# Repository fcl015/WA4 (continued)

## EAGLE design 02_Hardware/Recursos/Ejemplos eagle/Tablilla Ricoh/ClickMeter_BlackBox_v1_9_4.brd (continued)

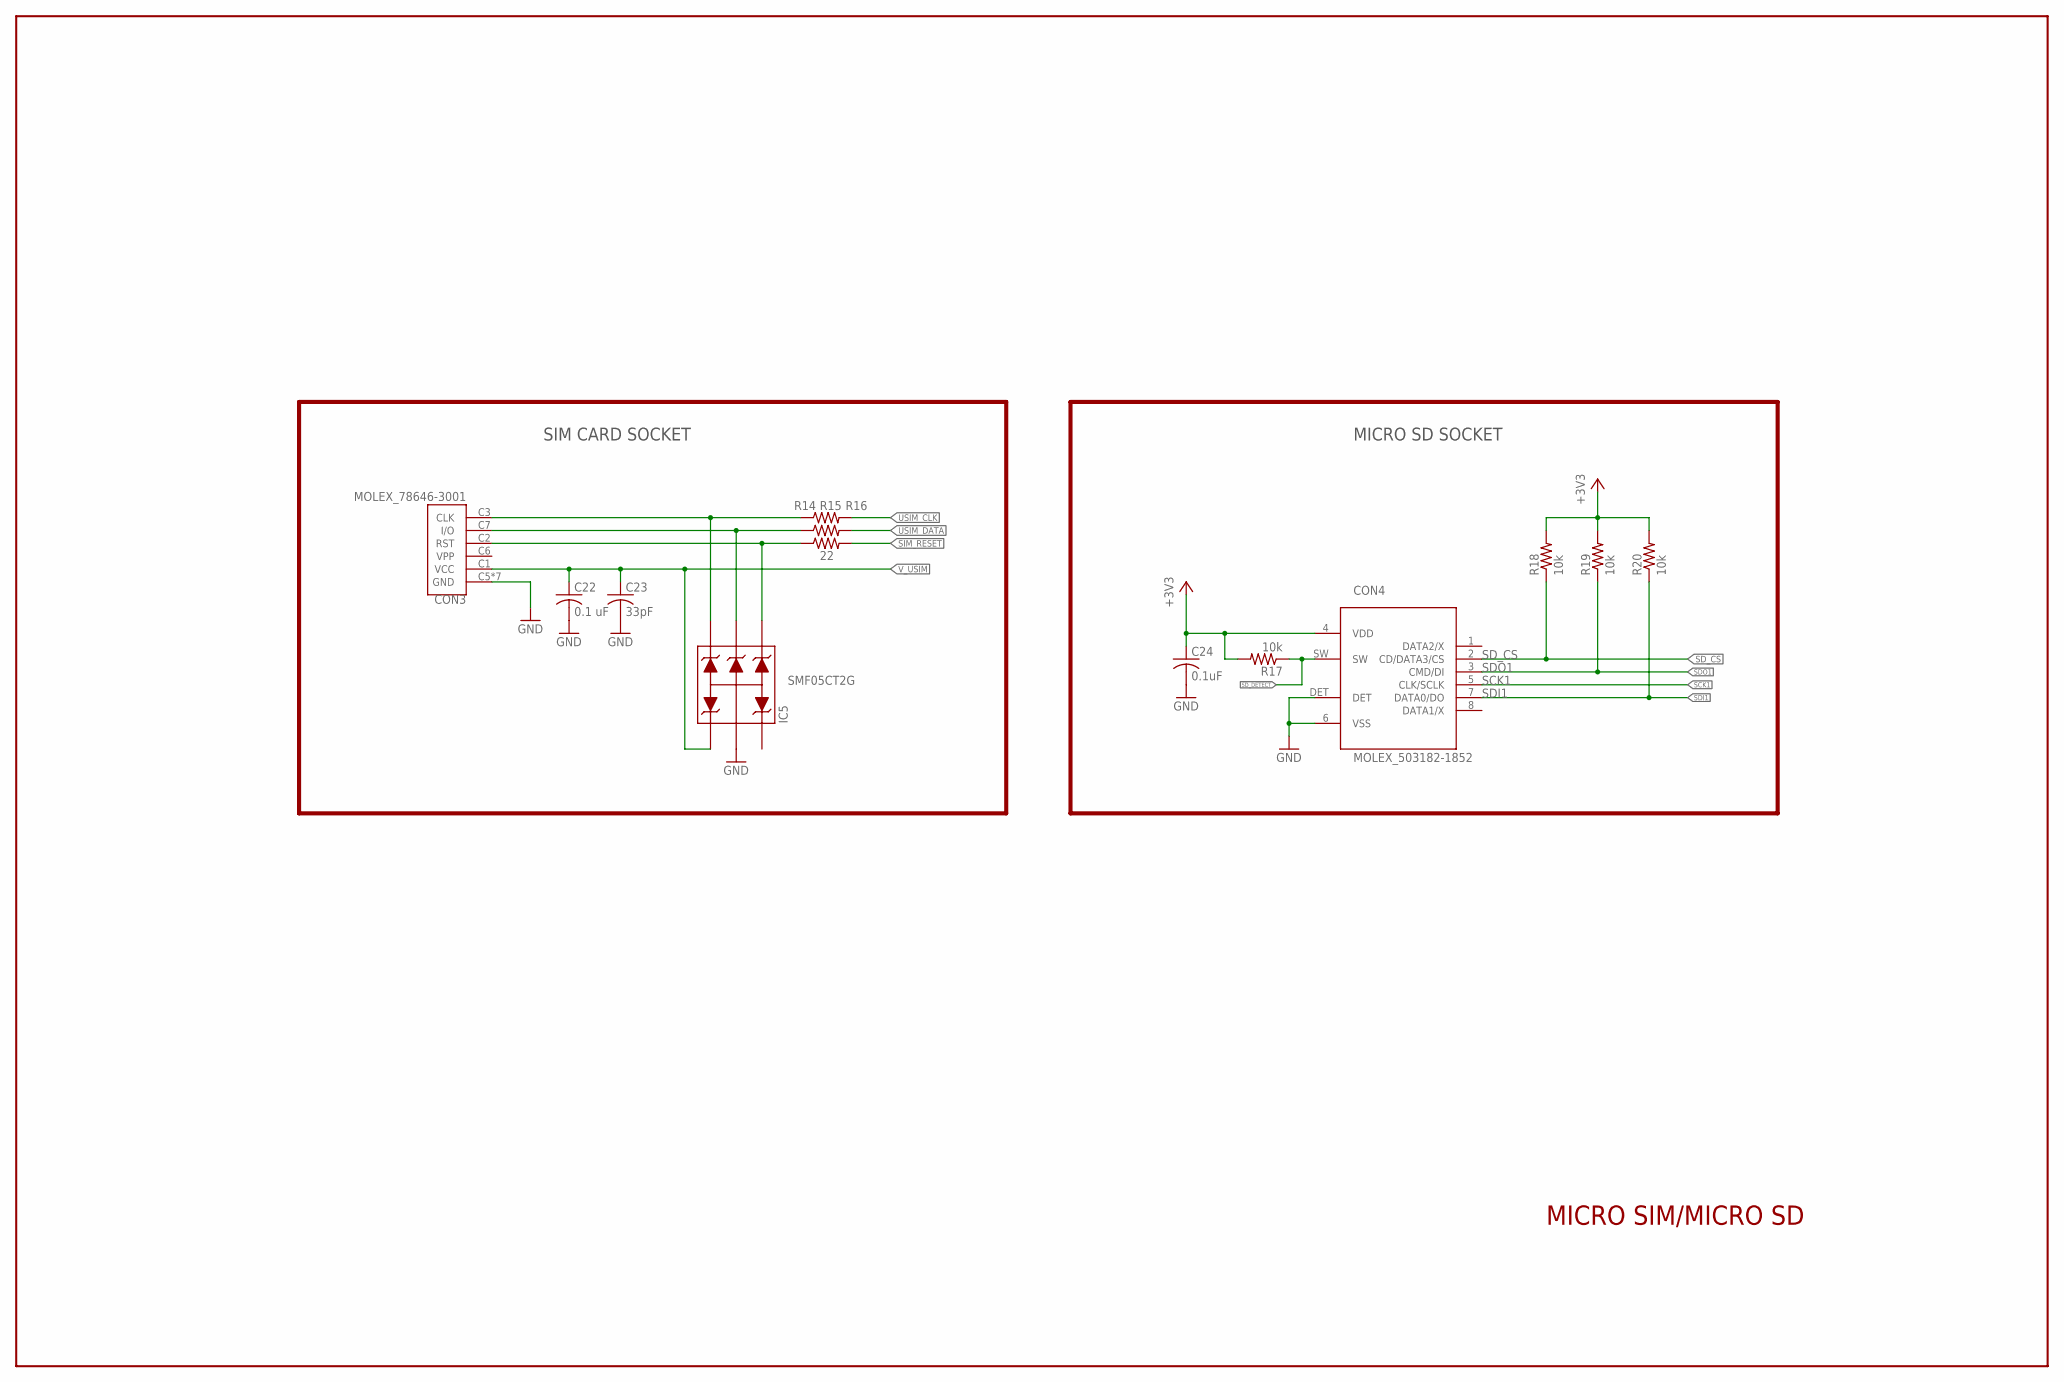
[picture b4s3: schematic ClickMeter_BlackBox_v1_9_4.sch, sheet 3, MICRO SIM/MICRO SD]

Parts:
C22: 0.1 uF; C0603
C23: 33pF; C0603
C24: 0.1uF; C0603
CON3: MOLEX_78646-3001
CON4: MOLEX_503182-1852
IC5: SMF05CT2G; SC-88/SC70-6/SOT-363
R14, R15, R16: 22; R0603
R17, R18, R19, R20: 10k; R0603

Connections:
+3V3: C24.1, CON4.4 (VDD), R17.2, R18.2, R19.2, R20.2; also elsewhere on the board
GND: C22.2, C23.2, C24.2, CON3.C5 (GND), CON3.GND1 (GND), CON3.GND2 (GND), CON3.GND3 (GND), CON3.GND4 (GND), CON3.GND5 (GND), CON3.GND6 (GND), CON4.6 (VSS), CON4.DET, IC5.2 (AN); also elsewhere on the board
unnamed: CON3.C3 (CLK), IC5.6 (C5), R14.1
unnamed: CON3.C7 (I/O), IC5.5 (C4), R15.1
unnamed: CON3.C2 (RST), IC5.4 (C3), R16.1
SCK1: CON4.5 (CLK/SCLK); also elsewhere on the board
SDI1: CON4.7 (DATA0/DO), R20.1; also elsewhere on the board
SDO1: CON4.3 (CMD/DI), R19.1; also elsewhere on the board
SD_CS: CON4.2 (CD/DATA3/CS), R18.1; also elsewhere on the board
SD_DETECT: CON4.SW, R17.1; also elsewhere on the board
SIM_RESET: R16.2; also elsewhere on the board
USIM_CLK: R14.2; also elsewhere on the board
USIM_DATA: R15.2; also elsewhere on the board
V_USIM: C22.1, C23.1, CON3.C1 (VCC), IC5.1 (C1); also elsewhere on the board

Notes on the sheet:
SIM CARD SOCKET
MICRO SD SOCKET
MICRO SIM/MICRO SD

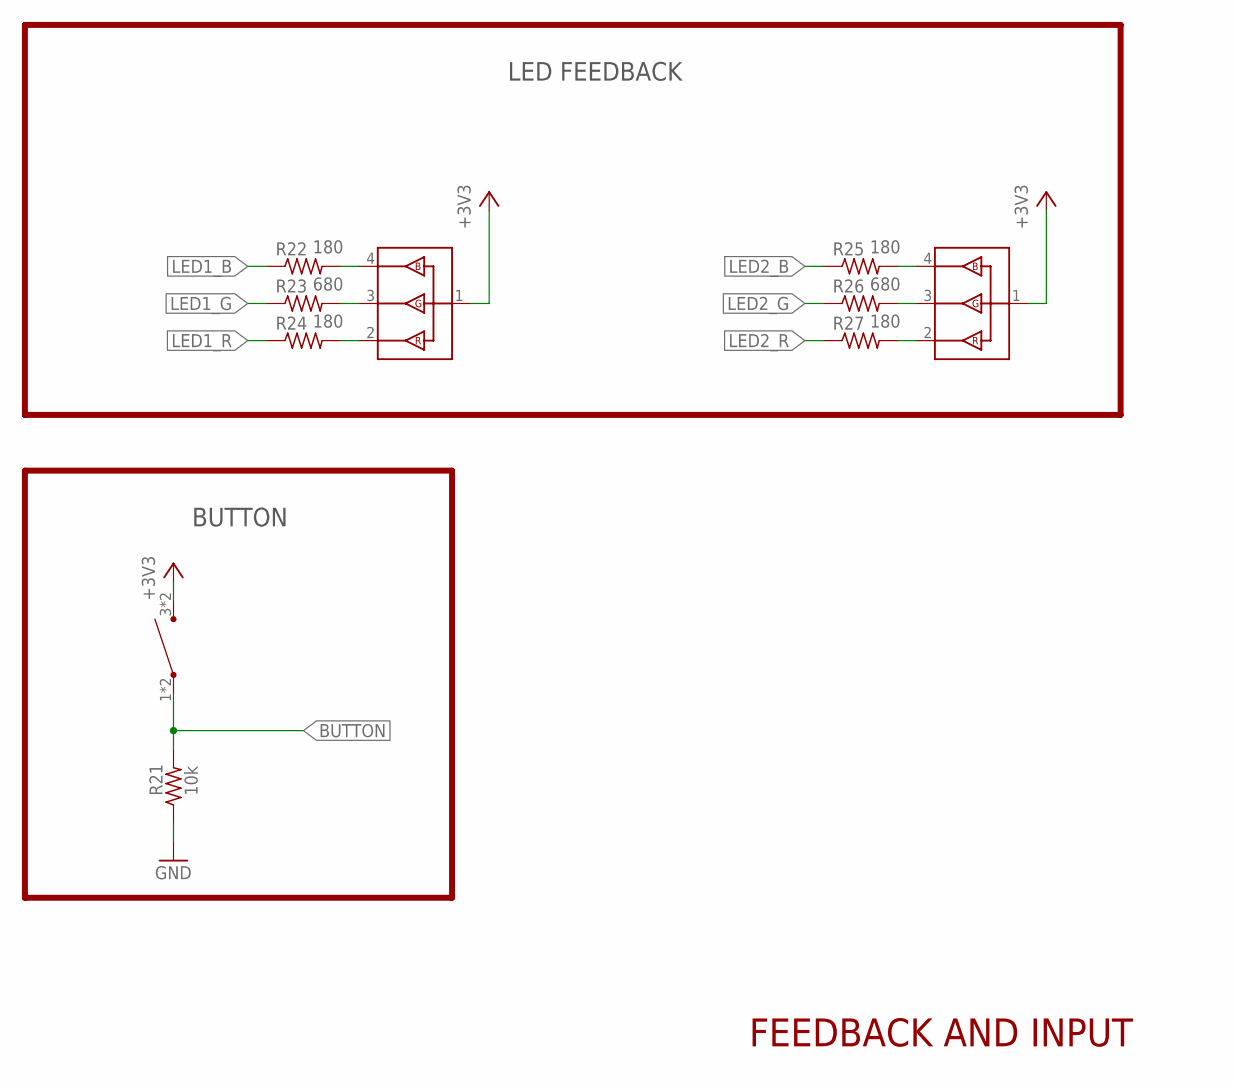
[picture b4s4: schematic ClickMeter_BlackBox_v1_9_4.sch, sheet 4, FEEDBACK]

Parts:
BT1: PTS525_SM15; PTS525SM15SMTR2
LED1, LED2: APTF1616SEEZGQBDC
R21: 10k; R0603
R22, R24, R25, R27: 180; R0603
R23, R26: 680; R0603

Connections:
+3V3: BT1.3, BT1.4, LED1.1, LED2.1; also elsewhere on the board
BUTTON: BT1.1, BT1.2, R21.2; also elsewhere on the board
GND: R21.1; also elsewhere on the board
LED1_B: R22.1; also elsewhere on the board
LED1_G: R23.1; also elsewhere on the board
LED1_R: R24.1; also elsewhere on the board
LED2_B: R25.1; also elsewhere on the board
LED2_G: R26.1; also elsewhere on the board
LED2_R: R27.1; also elsewhere on the board
unnamed: LED1.3, R23.2
unnamed: LED1.2, R24.2
unnamed: LED1.4, R22.2
unnamed: LED2.3, R26.2
unnamed: LED2.2, R27.2
unnamed: LED2.4, R25.2

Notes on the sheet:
FEEDBACK AND INPUT
LED FEEDBACK
BUTTON

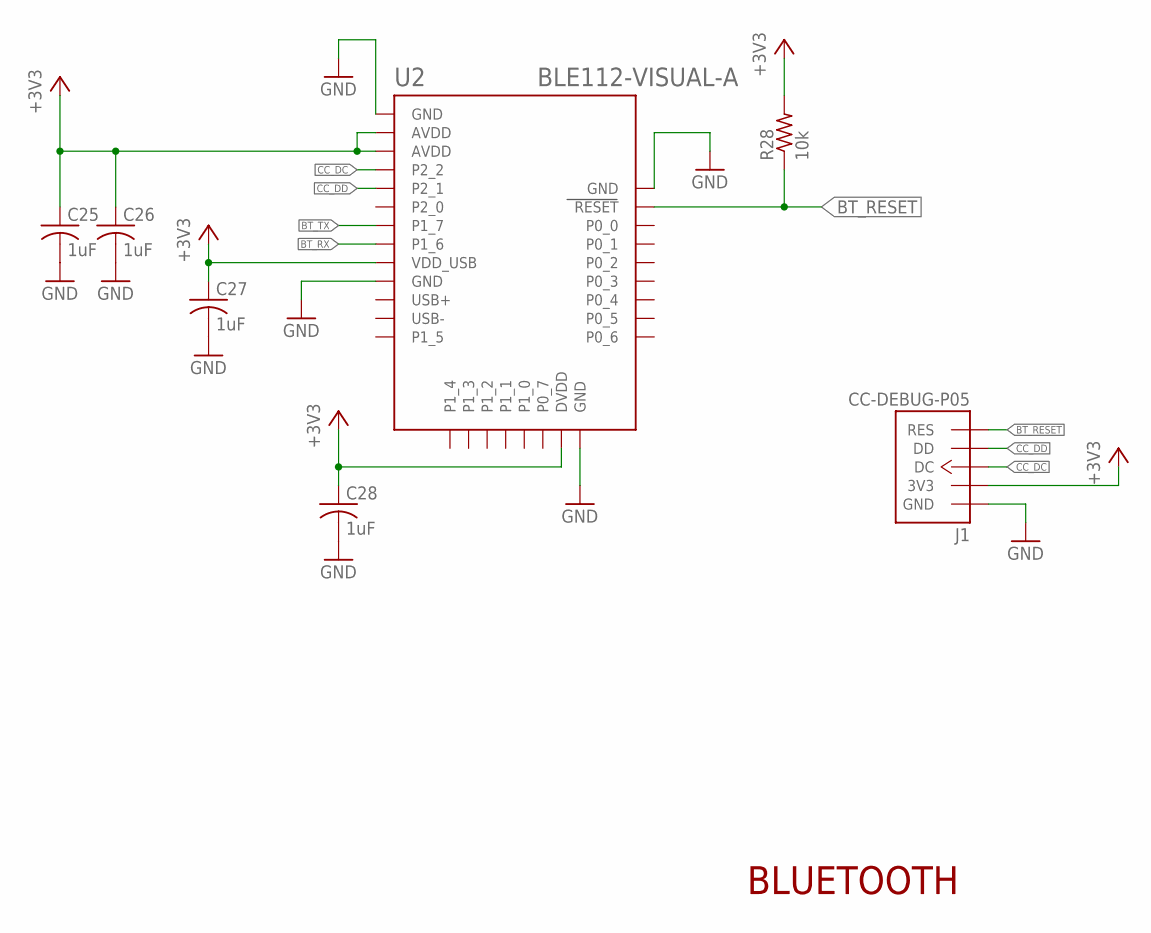
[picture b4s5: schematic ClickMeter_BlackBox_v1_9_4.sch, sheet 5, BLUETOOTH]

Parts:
C25, C26, C27, C28: 1uF; C0603
J1: CC-DEBUG-P05; CC-P05
R28: 10k; R0603
U2: BLE112-VISUAL-A; BLE112-A

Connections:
+3V3: C25.1, C26.1, C27.1, C28.1, J1.2 (3V3), R28.2, U2.AVDD, U2.AVDD@2 (AVDD), U2.DVDD, U2.VDD_USB; also elsewhere on the board
BT_RESET: J1.7 (RES), R28.1, U2.RESET; also elsewhere on the board
BT_RX: U2.P1_6; also elsewhere on the board
BT_TX: U2.P1_7; also elsewhere on the board
CC_DC: J1.3 (DC), U2.P2_2
CC_DD: J1.4 (DD), U2.P2_1
GND: C25.2, C26.2, C27.2, C28.2, J1.1 (GND), U2.GND, U2.GND@2 (GND), U2.GND@3 (GND), U2.GND@4 (GND); also elsewhere on the board

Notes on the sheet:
BLUETOOTH

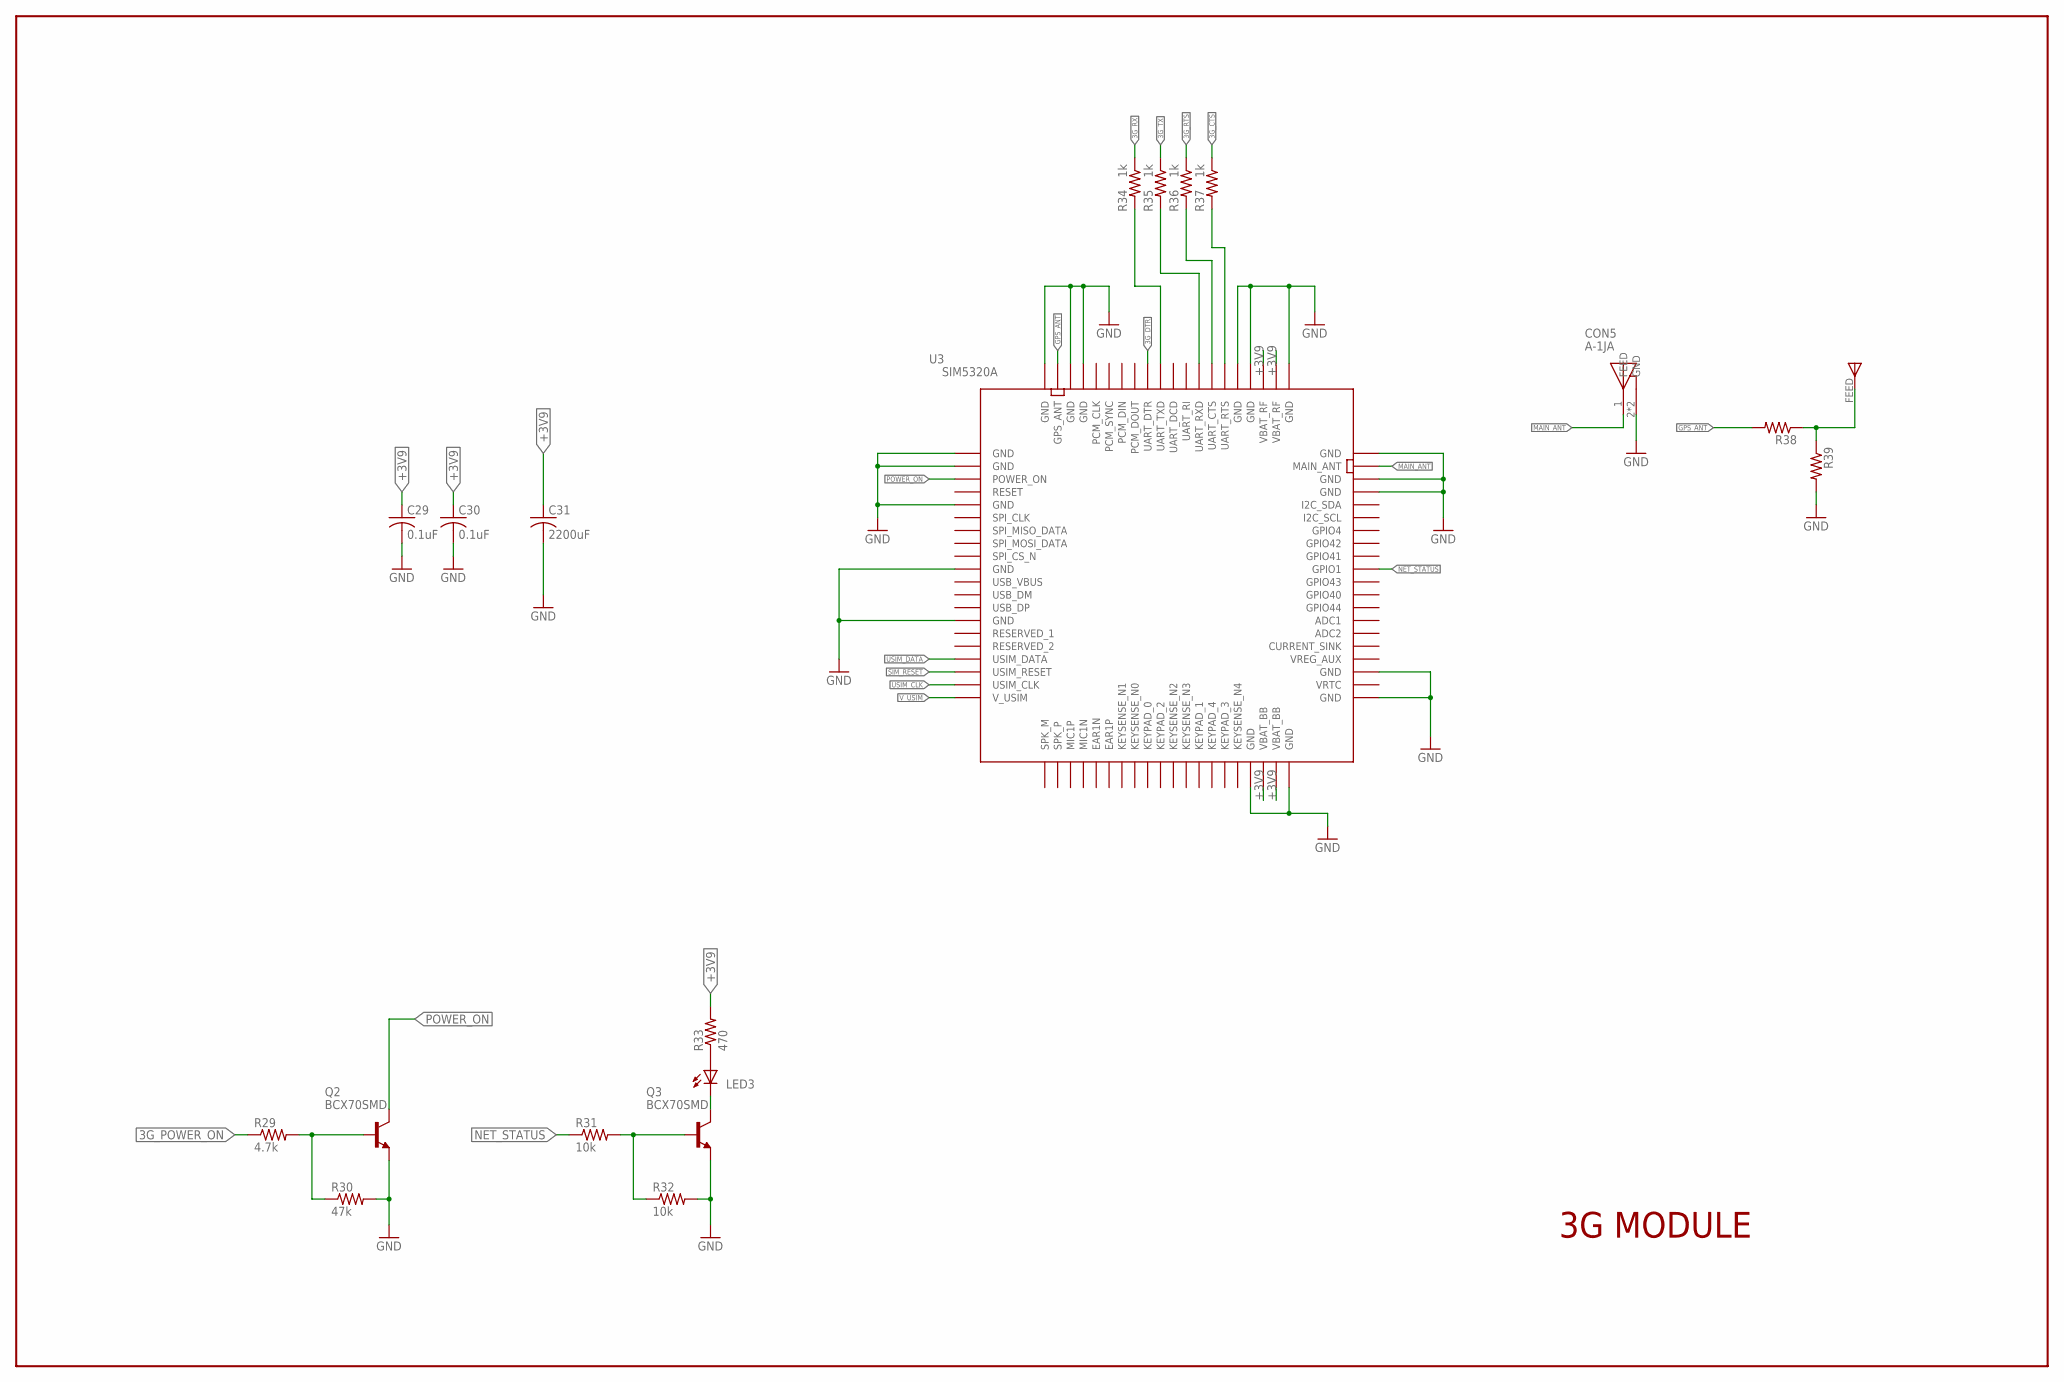
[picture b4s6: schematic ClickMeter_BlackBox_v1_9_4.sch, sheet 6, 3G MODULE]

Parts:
ANT1: 1575AT43A0040E
C29, C30: 0.1uF; C0603
C31: 2200uF; 592D-2200
CON5: A-1JA
LED3: LED_ESML0603; LED_SML0603
Q2, Q3: BCX70SMD; SOT23
R29: 4.7k; R0603
R30: 47k; R0603
R31, R32: 10k; R0603
R33: 470; R0603
R34, R35, R36, R37: 1k; R0402
R38, R39: R-US_R0402; R0402
U3: SIM5320A

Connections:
3G_CTS: R37.1; also elsewhere on the board
3G_DTR: U3.P$72 (UART_DTR); also elsewhere on the board
3G_POWER_ON: R29.1; also elsewhere on the board
3G_RTS: R36.1; also elsewhere on the board
3G_RX: R34.1; also elsewhere on the board
3G_TX: R35.1; also elsewhere on the board
+3V9: C29.1, C30.1, C31.1, R33.2, U3.P$38 (VBAT_BB), U3.P$39 (VBAT_BB), U3.P$62 (VBAT_RF), U3.P$63 (VBAT_RF); also elsewhere on the board
GND: C29.2, C30.2, C31.2, CON5.2 (GND), CON5.3 (GND), Q2.2 (E), Q3.2 (E), R30.2, R32.2, R39.2, U3.P$1 (GND), U3.P$2 (GND), U3.P$5 (GND), U3.P$10 (GND), U3.P$14 (GND), U3.P$37 (GND), U3.P$40 (GND), U3.P$41 (GND), U3.P$43 (GND), U3.P$57 (GND), U3.P$58 (GND), U3.P$60 (GND), U3.P$61 (GND), U3.P$64 (GND), U3.P$65 (GND), U3.P$77 (GND), U3.P$78 (GND), U3.P$80 (GND); also elsewhere on the board
GPS_ANT: R38.2, U3.P$79 (GPS_ANT)
MAIN_ANT: CON5.1 (FEED), U3.P$59 (MAIN_ANT)
unnamed: R34.2, U3.P$71 (UART_TXD)
unnamed: Q2.1 (B), R29.2, R30.1
unnamed: Q3.1 (B), R31.2, R32.1
unnamed: LED3.A, R33.1
unnamed: LED3.C, Q3.3 (C)
unnamed: ANT1.FEED, R38.1, R39.1
unnamed: R35.2, U3.P$68 (UART_RXD)
unnamed: R36.2, U3.P$67 (UART_CTS)
unnamed: R37.2, U3.P$66 (UART_RTS)
NET_STATUS: R31.1, U3.P$51 (GPIO1); also elsewhere on the board
POWER_ON: Q2.3 (C), U3.P$3 (POWER_ON)
SIM_RESET: U3.P$18 (USIM_RESET); also elsewhere on the board
USIM_CLK: U3.P$19 (USIM_CLK); also elsewhere on the board
USIM_DATA: U3.P$17 (USIM_DATA); also elsewhere on the board
V_USIM: U3.P$20 (V_USIM); also elsewhere on the board

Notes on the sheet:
3G MODULE

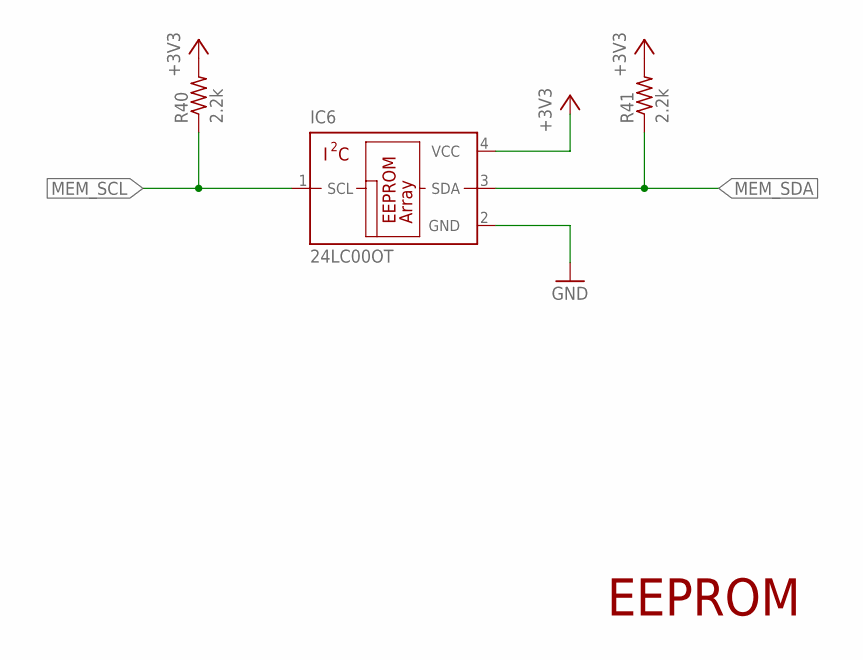
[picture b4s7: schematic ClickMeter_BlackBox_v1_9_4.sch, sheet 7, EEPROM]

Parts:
IC6: 24LC00OT; SOT23-5L
R40, R41: 2.2k; R0603

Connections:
+3V3: IC6.4 (VCC), R40.2, R41.2; also elsewhere on the board
GND: IC6.2 (GND); also elsewhere on the board
MEM_SCL: IC6.1 (SCL), R40.1; also elsewhere on the board
MEM_SDA: IC6.3 (SDA), R41.1; also elsewhere on the board

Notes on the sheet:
EEPROM

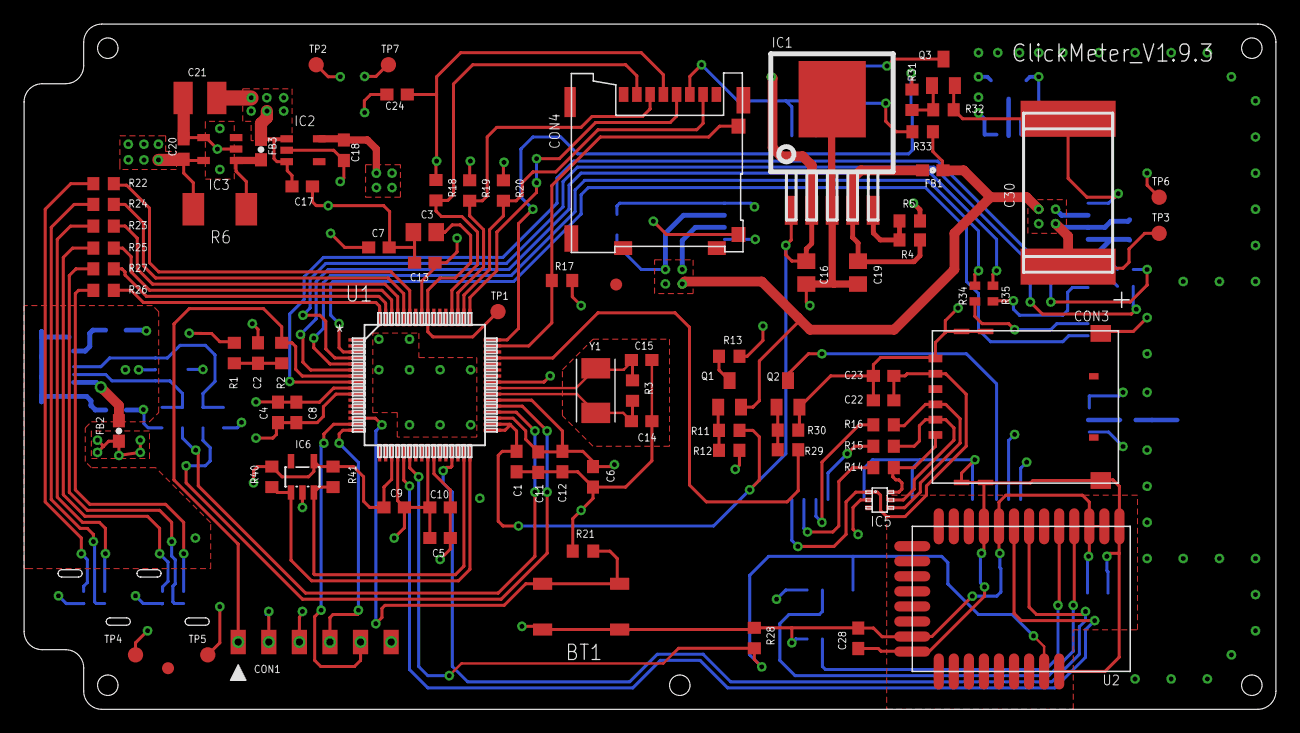
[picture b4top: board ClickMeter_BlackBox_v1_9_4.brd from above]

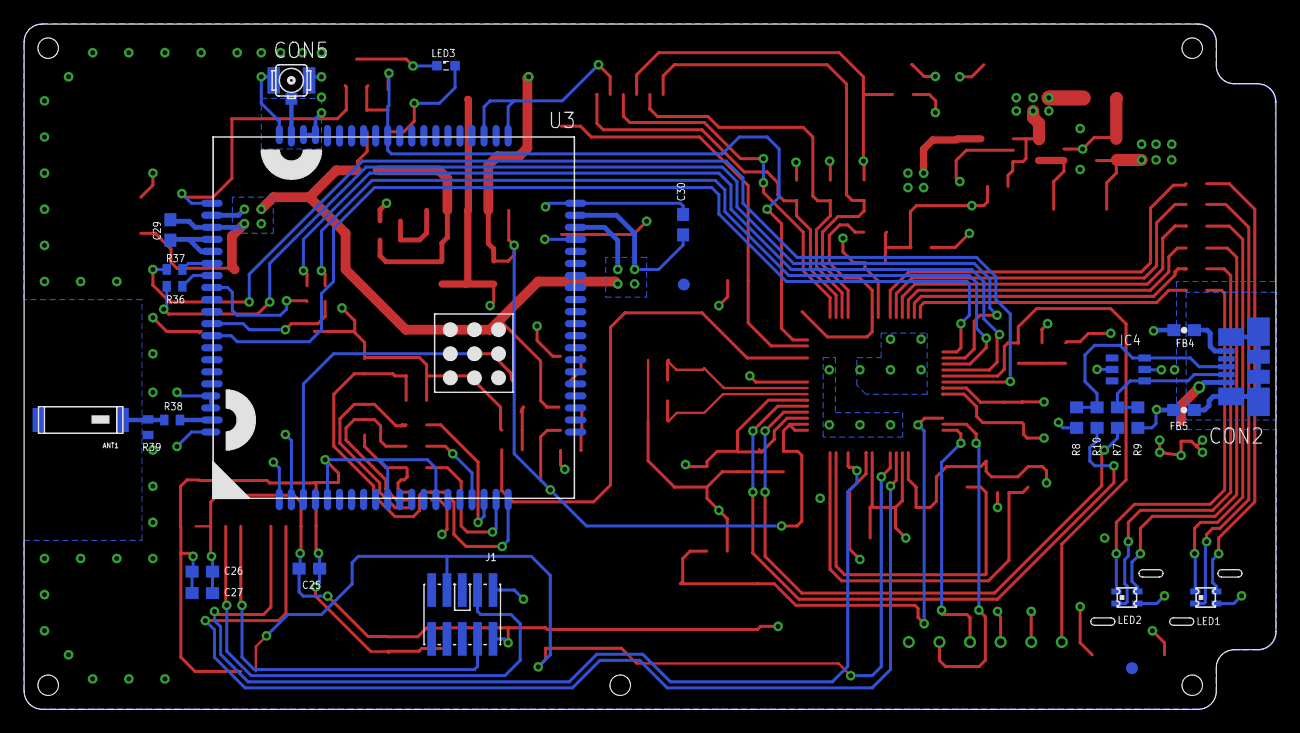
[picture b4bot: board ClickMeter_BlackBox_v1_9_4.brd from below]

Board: 4 copper layers, 104.0 x 56.9 mm, 112 parts (26 on the bottom side), 75 nets.

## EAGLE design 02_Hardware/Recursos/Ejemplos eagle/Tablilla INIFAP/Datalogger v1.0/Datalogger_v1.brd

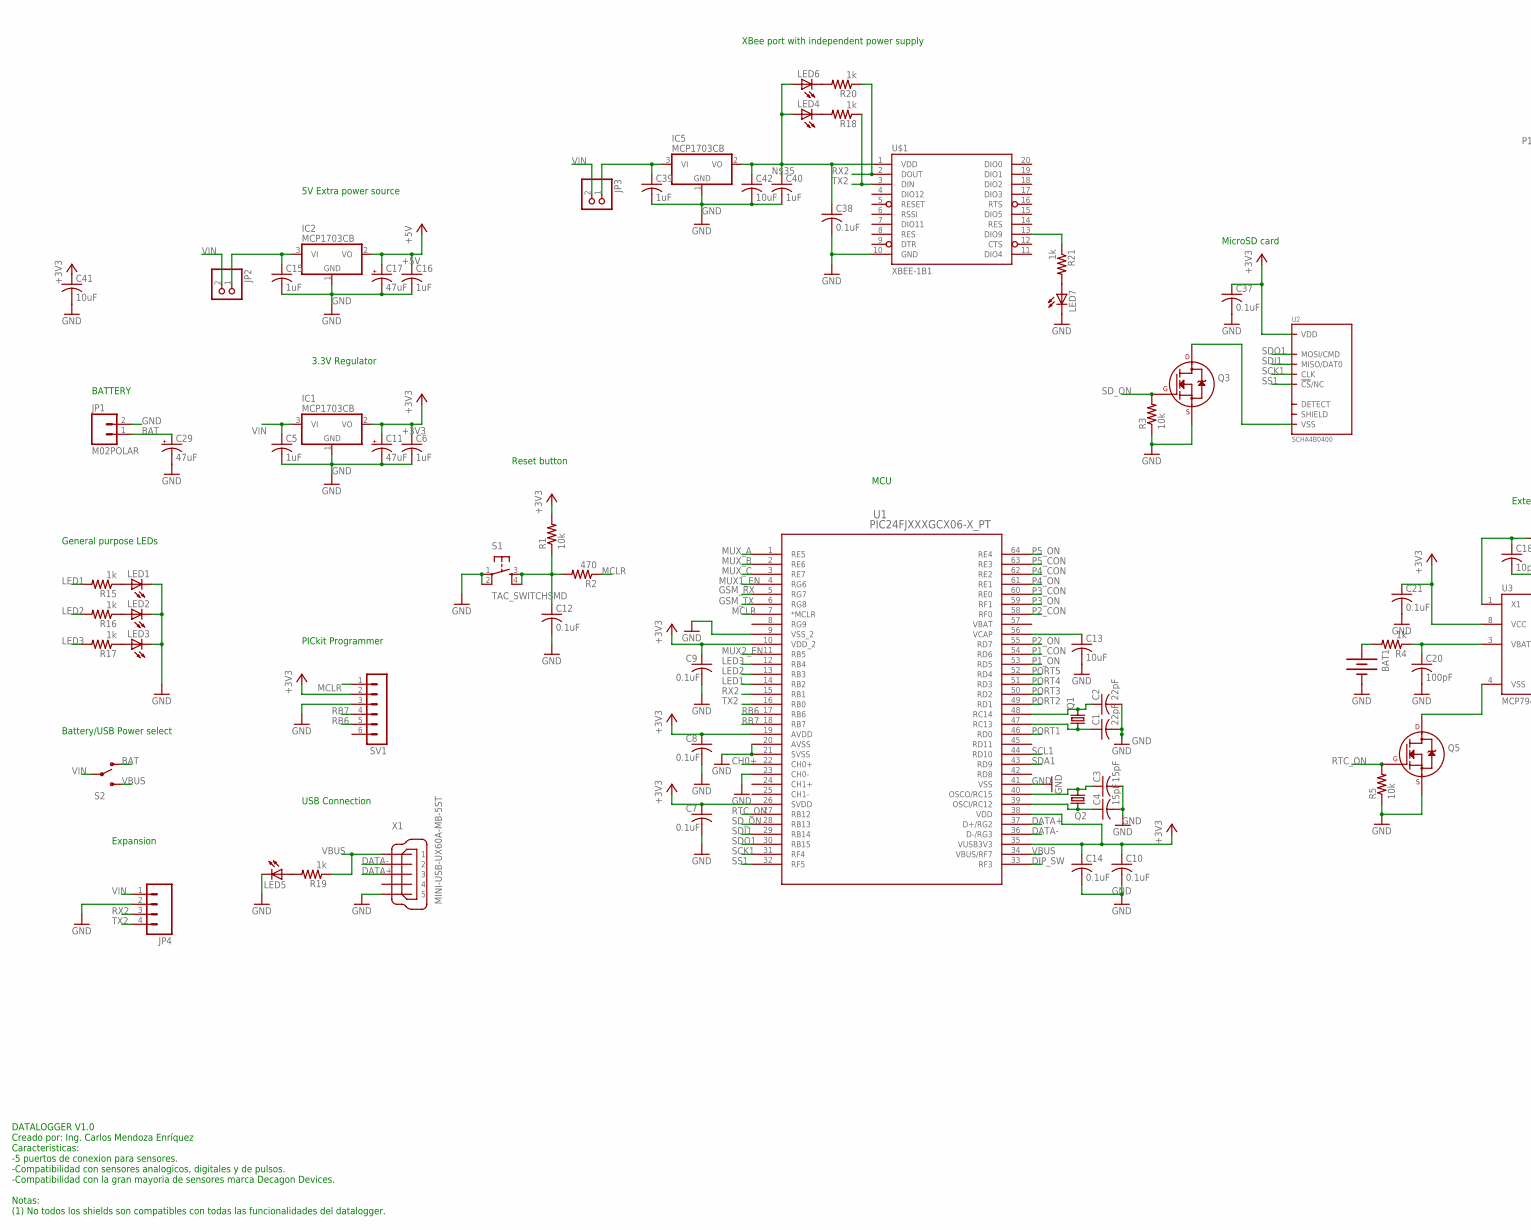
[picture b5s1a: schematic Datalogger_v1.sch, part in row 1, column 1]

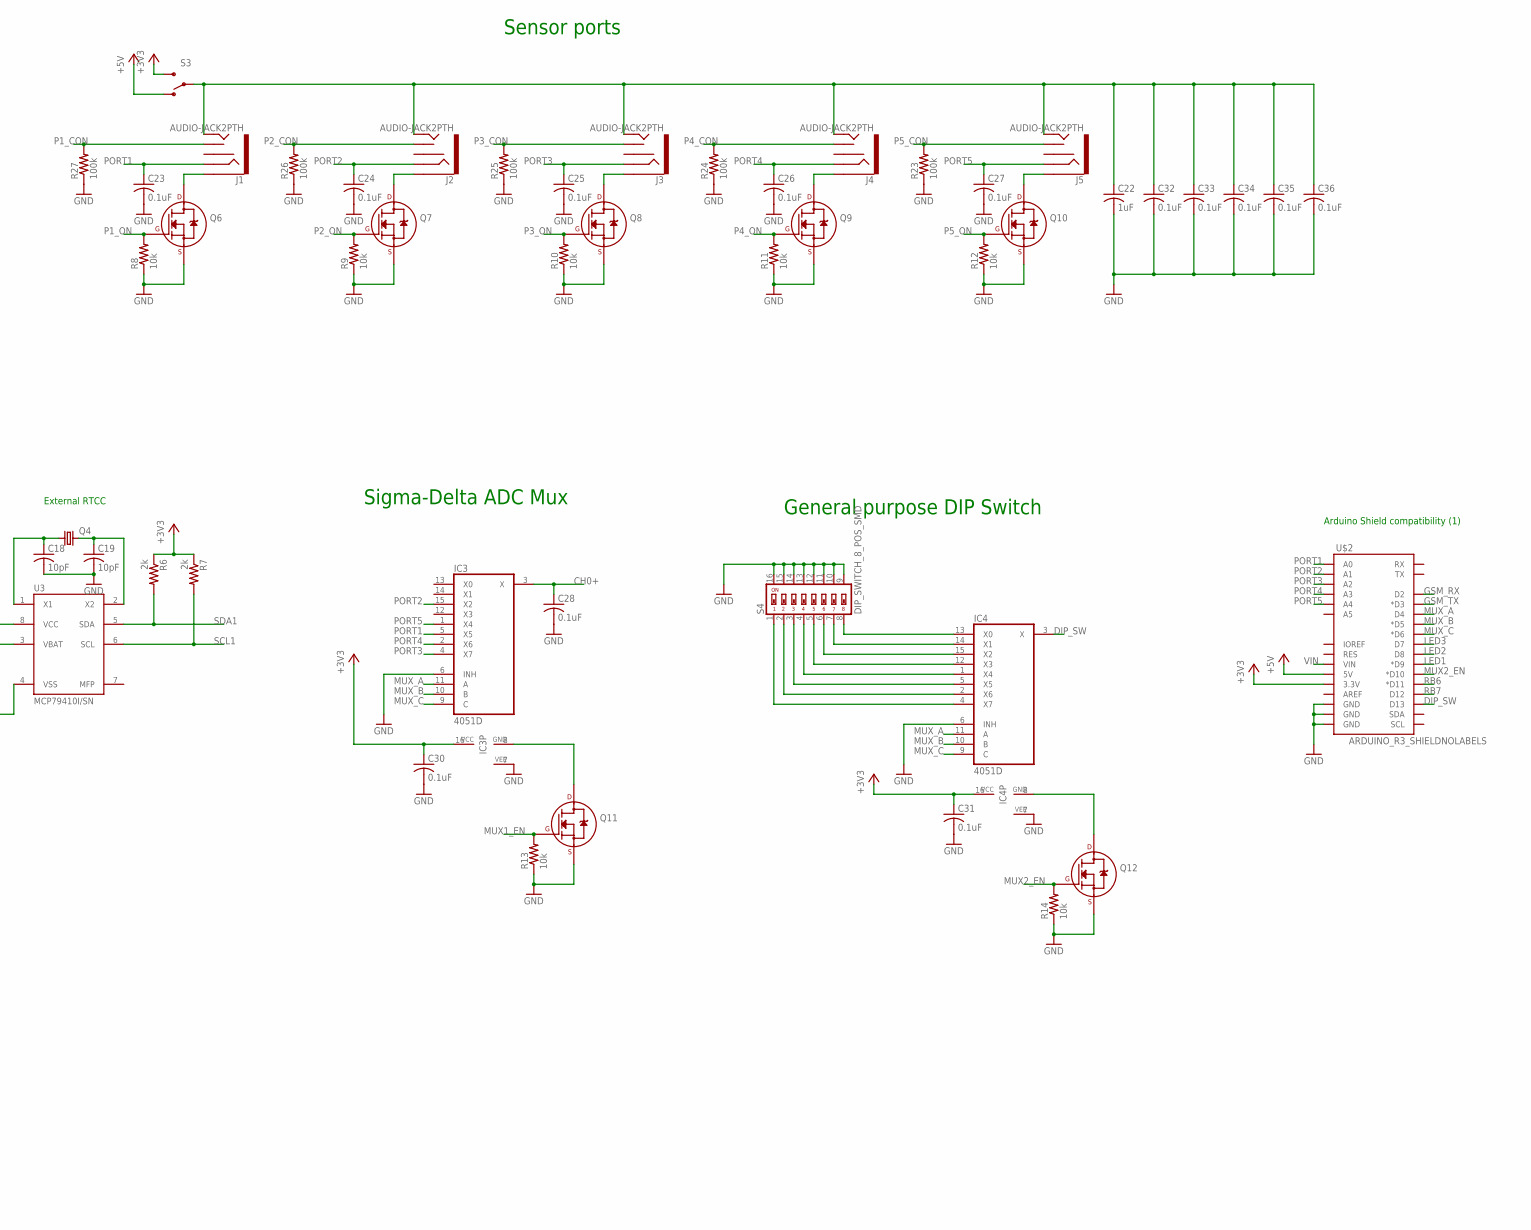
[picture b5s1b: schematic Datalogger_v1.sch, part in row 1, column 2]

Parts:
BAT1: BATTERY20PTH; BATTCOM_20MM_PTH
C1, C2: 22pF; C0603K
C3, C4: 15pF; C0603K
C5, C6, C15, C16, C22, C39, C40: 1uF; C0805K
C7, C8, C9, C10, C12, C14, C21, C23, C24, C25, C26, C27, C28, C30, C31, C32, C33, C34, C35, C36, C37, C38: 0.1uF; C0805K
C11, C17, C29: 47uF; 153CLV-0605
C13, C41, C42: 10uF; C0805K
C18, C19: 10pF; C0603K
C20: 100pF; C0805K
IC1, IC2, IC5: MCP1703CB; SOT23
IC3, IC4: 4051D; SO16
J1, J2, J3, J4, J5: AUDIO-JACK2PTH; AUDIO-JACK
JP1: M02POLAR; MOLEX-1X2
JP2, JP3: PINHD-1X2; 1X02
JP4: M04POLAR; MOLEX-1X4
LED1, LED2, LED3, LED4, LED5, LED6, LED7: LEDCHIPLED_0603; CHIPLED_0603
Q1, Q4: CRYSTALMM20SS; MM20SS
Q2: CSM-7X-DU
Q3, Q5, Q6, Q7, Q8, Q9, Q10, Q11, Q12: 2N7000_SOT23; SOT-23
R1, R3, R5, R8, R9, R10, R11, R12, R13, R14: 10k; R0805
R2: 470; R0805
R4, R15, R16, R17, R18, R19, R20, R21: 1k; R0805
R6, R7: 2k; R0805
R23, R24, R25, R26, R27: 100k; R0805
S1: TAC_SWITCHSMD; TACTILE-SWITCH-SMD
S2, S3: SWITCH-SPDT-SMD-A; SWITCH-SPST-SMD-A
S4: DIP_SWITCH_8_POS_SMD; SWITCH_04
SV1: MA06-1
U1: PIC24FJXXXGCX06-X_PT; TQFP64_10X10MC
U2: SCHA4B0400
U3: MCP79410I/SN; SO8
U$1: XBEE-1B1; XBEE-1
U$2: ARDUINO_R3_SHIELDNOLABELS; UNO_R3_SHIELD_NOLABELS
X1: MINI-USB-UX60A-MB-5ST; UX60A-MB-5ST

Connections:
+3V3: C6.1, C7.1, C8.1, C9.1, C10.1, C11.+, C14.1, C21.1, C30.1, C31.1, C37.1, C41.1, IC1.2 (VO), IC3.16 (VCC), IC4.16 (VCC), R1.2, R6.1, R7.1, S3.3 (S), SV1.2, U1.10 (VDD_2), U1.19 (AVDD), U1.26 (SVDD), U1.35 (VUSB3V3), U1.38 (VDD), U2.VDD, U3.8 (VCC), U$2.3.3V
+5V: C16.1, C17.+, IC2.2 (VO), S3.1 (O), U$2.5V
AS_RESET: C12.1, R1.1, R2.2, S1.3, S1.4
BAT: C29.+, JP1.1, S2.1 (O)
CH0+: C28.1, IC3.3 (X), U1.22 (CH0+)
DATA+: U1.37 (D+/RG2), X1.3
DATA-: U1.36 (D-/RG3), X1.2
DIP_SW: IC4.3 (X), U1.33 (RF3), U$2.D13
GND: BAT1.2 (-), C1.2, C2.2, C3.2, C4.2, C5.2, C6.2, C7.2, C8.2, C9.2, C10.2, C11.-, C12.2, C13.2, C14.2, C15.2, C16.2, C17.-, C18.2, C19.2, C20.2, C21.2, C22.2, C23.2, C24.2, C25.2, C26.2, C27.2, C28.2, C29.-, C30.2, C31.2, C32.2, C33.2, C34.2, C35.2, C36.2, C37.2, C38.2, C39.2, C40.2, C41.2, C42.2, IC1.1 (GND), IC2.1 (GND), IC3.6 (INH), IC3.7 (VEE), IC4.6 (INH), IC4.7 (VEE), IC5.1 (GND), JP1.2, JP4.2, LED1.C, LED2.C, LED3.C, LED5.C, LED7.C, Q3.2 (S), Q5.2 (S), Q6.2 (S), Q7.2 (S), Q8.2 (S), Q9.2 (S), Q10.2 (S), Q11.2 (S), Q12.2 (S), R3.1, R5.1, R8.1, R9.1, R10.1, R11.1, R12.1, R13.1, R14.1, R23.1, R24.1, R25.1, R26.1, R27.1, S1.1, S1.2, S4.9, S4.10, S4.11, S4.12, S4.13, S4.14, S4.15, S4.16, SV1.3, U1.9 (VSS_2), U1.20 (AVSS), U1.21 (SVSS), U1.23 (CH0-), U1.41 (VSS), U$1.10 (GND), U$2.GND@0 (GND), U$2.GND@1 (GND), U$2.GND@2 (GND), X1.5
GSM_RX: U1.5 (RG7), U$2.D2
GSM_TX: U1.6 (RG8), U$2.D3 (*D3)
LED1: R15.2, U1.14 (RB2), U$2.D9 (*D9)
LED2: R16.2, U1.13 (RB3), U$2.D8
LED3: R17.2, U1.12 (RB4), U$2.D7
MCLR: R2.1, SV1.1, U1.7 (*MCLR)
MUX1_EN: Q11.1 (G), R13.2, U1.4 (RG6)
MUX2_EN: Q12.1 (G), R14.2, U1.11 (RB5), U$2.D10 (*D10)
MUX_A: IC3.11 (A), IC4.11 (A), U1.1 (RE5), U$2.D4
MUX_B: IC3.10 (B), IC4.10 (B), U1.2 (RE6), U$2.D5 (*D5)
MUX_C: IC3.9 (C), IC4.9 (C), U1.3 (RE7), U$2.D6 (*D6)
unnamed: C3.1, Q2.2, U1.40 (OSCO/RC15)
unnamed: C4.1, Q2.1, U1.39 (OSCI/RC12)
unnamed: C2.1, Q1.4 (2), U1.48 (RC14)
unnamed: C1.1, Q1.1, U1.47 (RC13)
unnamed: C15.1, IC2.3 (VI), JP2.1
unnamed: LED1.A, R15.1
unnamed: BAT1.1 (+), R4.2
unnamed: C18.1, Q4.1, U3.1 (X1)
unnamed: C13.1, U1.56 (VCAP)
unnamed: Q3.3 (D), U2.GND (VSS), U2.GND@1 (VSS), U2.GND@2 (VSS), U2.VSS
unnamed: C39.1, IC5.3 (VI), JP3.1
unnamed: C19.1, Q4.4 (2), U3.2 (X2)
unnamed: C20.1, R4.1, U3.3 (VBAT)
unnamed: Q5.3 (D), U3.4 (VSS)
unnamed: J1.SLEEVE, Q6.3 (D)
unnamed: IC4.8 (GND), Q12.3 (D)
unnamed: J2.SLEEVE, Q7.3 (D)
unnamed: C22.1, C32.1, C33.1, C34.1, C35.1, C36.1, J1.TIP, J2.TIP, J3.TIP, J4.TIP, J5.TIP, S3.2
unnamed: IC3.8 (GND), Q11.3 (D)
unnamed: J3.SLEEVE, Q8.3 (D)
unnamed: IC4.4 (X7), S4.1
unnamed: J4.SLEEVE, Q9.3 (D)
unnamed: IC4.2 (X6), S4.2
unnamed: J5.SLEEVE, Q10.3 (D)
unnamed: IC4.5 (X5), S4.3
unnamed: IC4.1 (X4), S4.4
unnamed: IC4.12 (X3), S4.5
unnamed: IC4.15 (X2), S4.6
unnamed: IC4.14 (X1), S4.7
unnamed: IC4.13 (X0), S4.8
unnamed: LED2.A, R16.1
unnamed: LED3.A, R17.1
unnamed: LED5.A, R19.2
unnamed: C38.1, C40.1, C42.1, IC5.2 (VO), LED4.A, LED6.A, U$1.1 (VDD)
unnamed: LED4.C, R18.2
unnamed: LED6.C, R20.2
unnamed: LED7.A, R21.2
unnamed: R21.1, U$1.13 (DIO9)
P1_CON: J1.TSH, R27.2, U1.54 (RD6)
P1_ON: Q6.1 (G), R8.2, U1.53 (RD5)
P2_CON: J2.TSH, R26.2, U1.58 (RF0)
P2_ON: Q7.1 (G), R9.2, U1.55 (RD7)
P3_CON: J3.TSH, R25.2, U1.60 (RE0)
P3_ON: Q8.1 (G), R10.2, U1.59 (RF1)
P4_CON: J4.TSH, R24.2, U1.62 (RE2)
P4_ON: Q9.1 (G), R11.2, U1.61 (RE1)
P5_CON: J5.TSH, R23.2, U1.63 (RE3)
P5_ON: Q10.1 (G), R12.2, U1.64 (RE4)
PORT1: C23.1, IC3.5 (X5), J1.RING, U1.46 (RD0), U$2.A0
PORT2: C24.1, IC3.15 (X2), J2.RING, U1.49 (RD1), U$2.A1
PORT3: C25.1, IC3.4 (X7), J3.RING, U1.50 (RD2), U$2.A2
PORT4: C26.1, IC3.2 (X6), J4.RING, U1.51 (RD3), U$2.A3
PORT5: C27.1, IC3.1 (X4), J5.RING, U1.52 (RD4), U$2.A4
RB6: SV1.5, U1.17 (RB6), U$2.D11 (*D11)
RB7: SV1.4, U1.18 (RB7), U$2.D12
RTC_ON: Q5.1 (G), R5.2, U1.27 (RB12)
RX2: JP4.3, R20.1, U1.15 (RB1), U$1.2 (DOUT)
SCK1: U1.31 (RF4), U2.CLK
SCL1: R7.2, U1.44 (RD10), U3.6 (SCL)
SDA1: R6.2, U1.43 (RD9), U3.5 (SDA)
SDI1: U1.29 (RB14), U2.MISO/DAT0
SDO1: U1.30 (RB15), U2.MOSI/CMD
SD_ON: Q3.1 (G), R3.2, U1.28 (RB13)
SS1: U1.32 (RF5), U2.!CS!/NC/DAT3 (!CS!/NC)
TX2: JP4.4, R18.1, U1.16 (RB0), U$1.3 (DIN)
VBAT: U1.57 (VBAT)
VBUS: R19.1, S2.3 (S), U1.34 (VBUS/RF7), X1.1
VIN: C5.1, IC1.3 (VI), JP2.2, JP3.2, JP4.1, S2.2, U$2.VIN

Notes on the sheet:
PICkit Programmer
3.3V Regulator
Reset button
USB Connection
Battery/USB Power select
BATTERY
5V Extra power source
MCU
MicroSD card
External RTCC
DATALOGGER V1.0 Creado por: Ing. Carlos Mendoza Enríquez Caracteristicas: -5 puertos de conexion para sensores. -Compatibilidad con sensores analogicos, digitales y de pulsos. -Compatibilidad con la gran mayoria de sensores marca Decagon Devices. Notas: (1) No todos los shields son compatibles con 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
Sensor ports
Sigma-Delta ADC Mux
General purpose DIP Switch
General purpose LEDs
Expansion
Arduino Shield compatibility (1)
XBee port with independent power supply

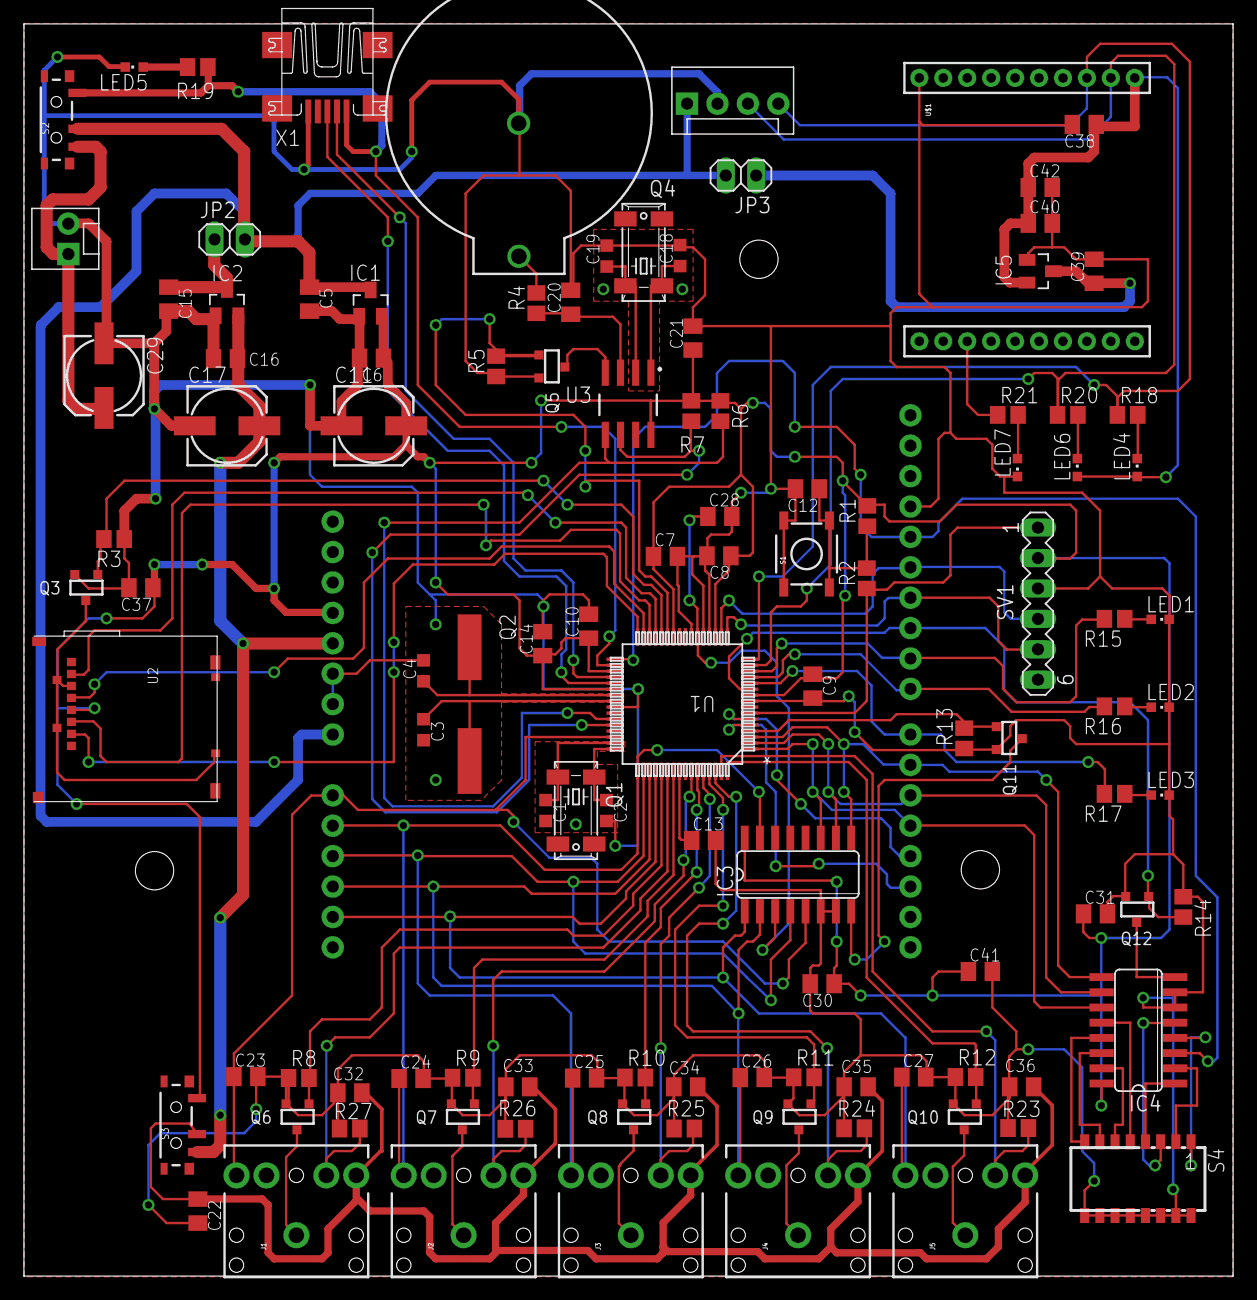
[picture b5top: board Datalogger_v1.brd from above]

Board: 2 copper layers, 101.0 x 104.6 mm, 113 parts (0 on the bottom side), 87 nets.
